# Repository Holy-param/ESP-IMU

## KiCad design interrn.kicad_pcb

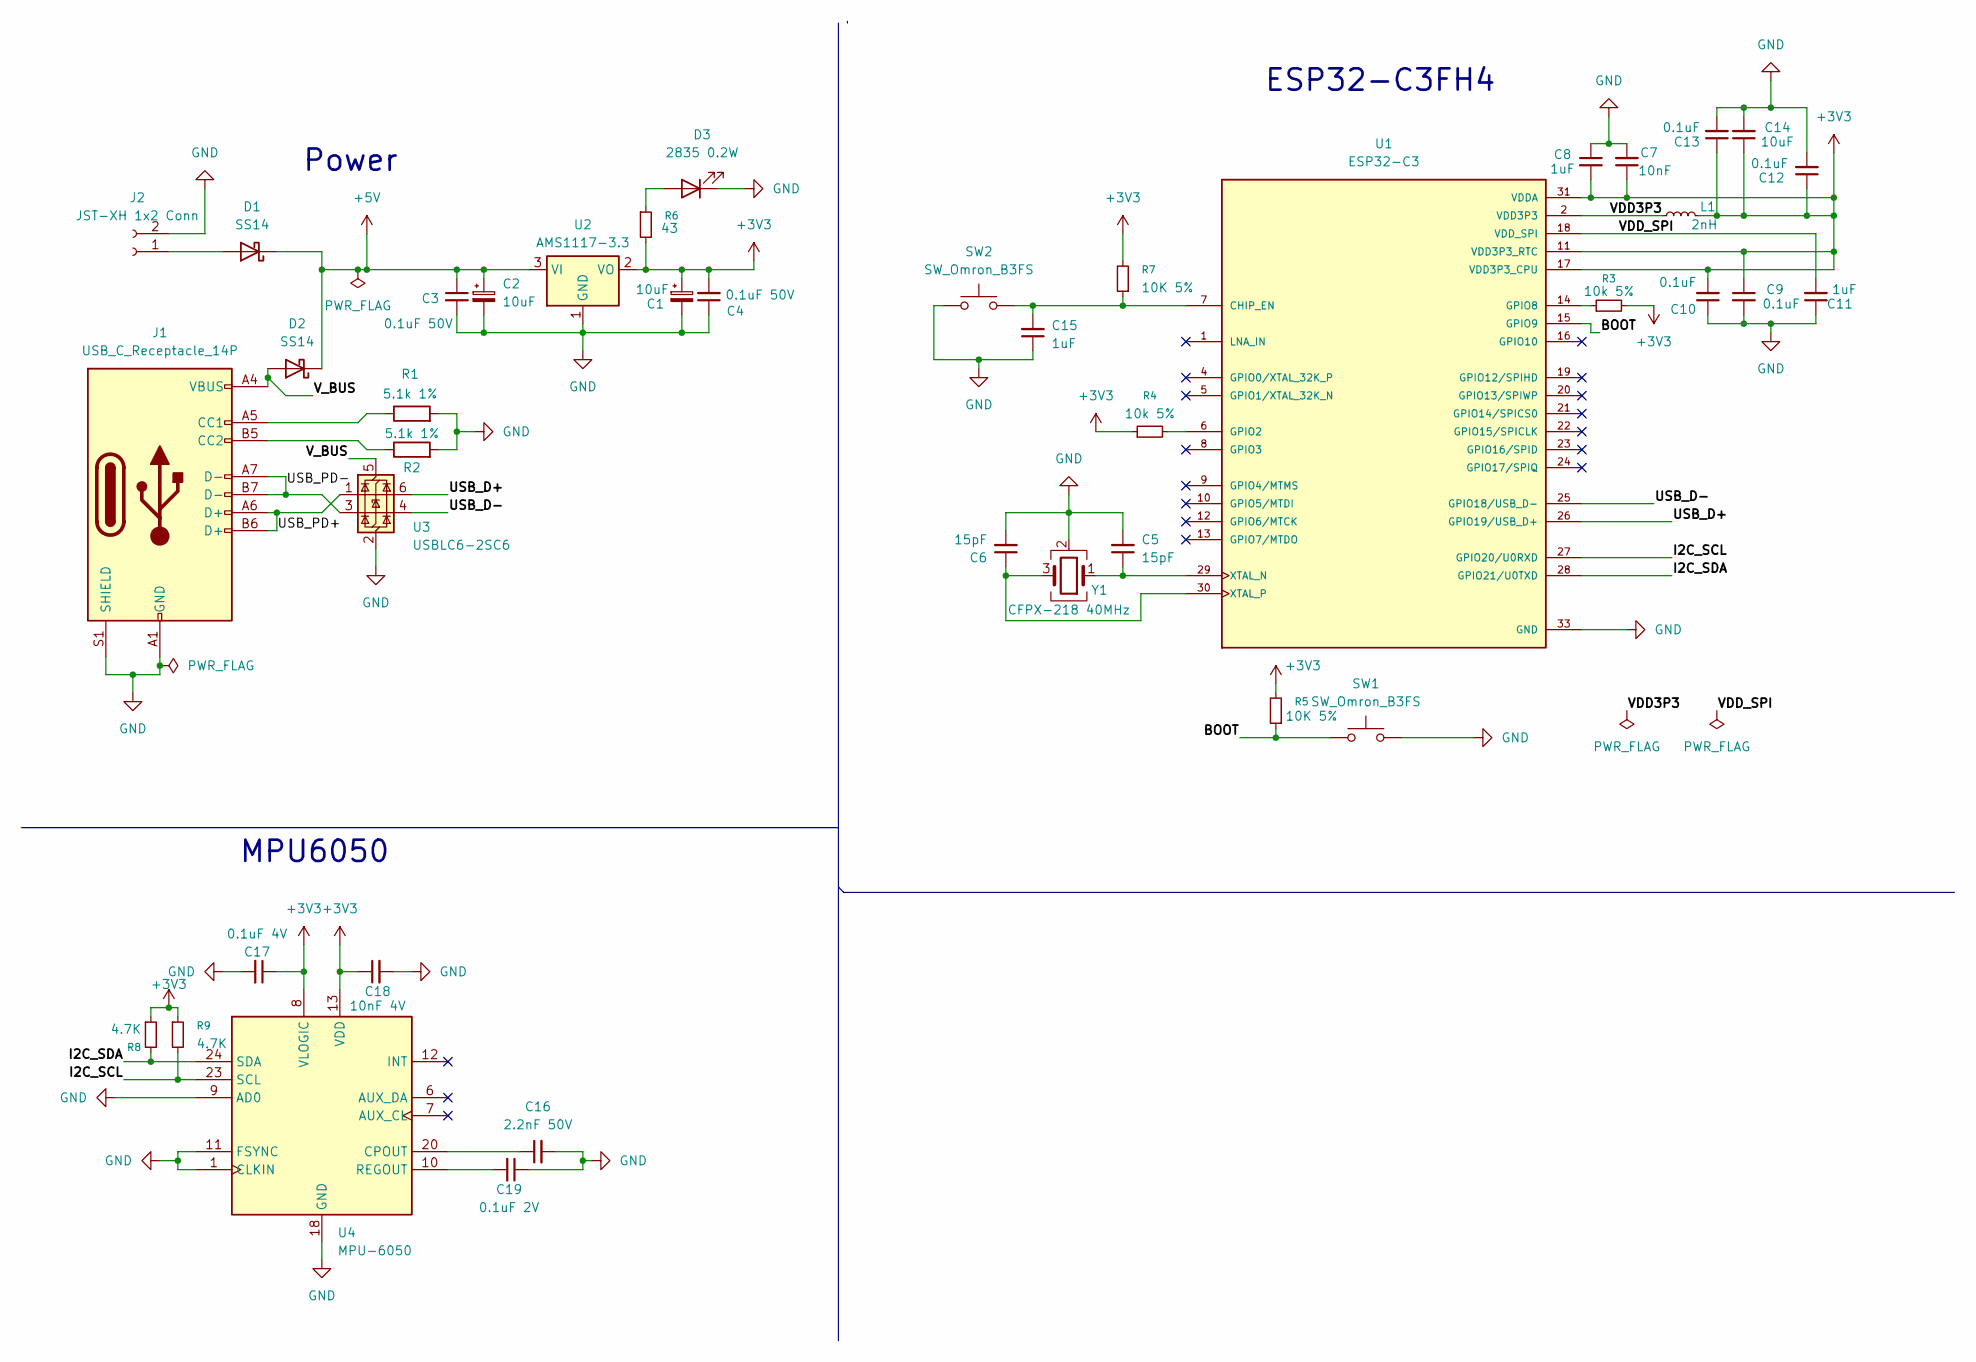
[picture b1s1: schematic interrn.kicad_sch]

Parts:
C1, C2: 10uF; CP_EIA-7343-15_Kemet-W
C3, C4: 0.1uF 50V; C_0402_1005Metric_Pad0.74x0.62mm_HandSolder
C5, C6: 15pF; C_0402_1005Metric
C7: 10nF; C_0402_1005Metric
C8, C11, C15: 1uF; C_0402_1005Metric
C9, C10, C12, C13: 0.1uF; C_0402_1005Metric
C14: 10uF; C_0402_1005Metric
C16: 2.2nF 50V; C_0402_1005Metric
C17: 0.1uF 4V; C_0402_1005Metric
C18: 10nF 4V; C_0402_1005Metric
C19: 0.1uF 2V; C_0402_1005Metric
D1, D2: SS14; D_SMA
D3: 2835 0.2W; LED_PLCC_2835
J1: USB_C_Receptacle_14P; USB_C_Receptacle_G-Switch_GT-USB-7010ASV
J2: JST-XH 1x2 Conn; JST_XH_B2B-XH-AM_1x02_P2.50mm_Vertical
L1: 2nH; L_0402_1005Metric
R1, R2: 5.1k 1%; R_0402_1005Metric
R3, R4: 10k 5%; R_0402_1005Metric
R5, R7: 10K 5%; R_0402_1005Metric
R6: 43; R_0402_1005Metric
R8, R9: 4.7K; R_0402_1005Metric
SW1, SW2: SW_Omron_B3FS; SW_SPST_Omron_B3FS-100xP
U1: ESP32-C3; QFN50P500X500X90-33N; MPN ESP32-C3
U2: AMS1117-3.3; SOT-223-3_TabPin2
U3: USBLC6-2SC6; SOT-23-6
U4: MPU-6050; InvenSense_QFN-24_4x4mm_P0.5mm
Y1: CFPX-218 40MHz; Crystal_SMD_WE_CFPX-218-4Pin_2.5x2.0mm

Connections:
+3V3: C1.1, C4.2, C7.1, C8.2, C9.1, C10.2, C12.1, C13.1, C14.1, C17.1, C18.1, L1.2, R3.2, R4.1, R5.2, R6.2, R7.2, R8.1, R9.1, U1.11 (VDD3P3_RTC), U1.17 (VDD3P3_CPU), U1.31 (VDDA), U1.32 (VDDA), U2.2 (VO), U4.8 (VLOGIC), U4.13 (VDD)
+5V: C2.1, C3.1, D1.1 (K), D2.1 (K), U2.3 (VI)
/BOOT: R5.1, SW1.1, U1.15 (GPIO9)
/I2C_SCL: R9.2, U1.27 (GPIO20/U0RXD), U4.23 (SCL)
/I2C_SDA: R8.2, U1.28 (GPIO21/U0TXD), U4.24 (SDA)
/USB_D+: U1.26 (GPIO19/USB_D+), U3.6 (I/O1)
/USB_D-: U1.25 (GPIO18/USB_D-), U3.4 (I/O2)
/USB_PD+: J1.A6 (D+), J1.B6 (D+), U3.1 (I/O1)
/USB_PD-: J1.A7 (D-), J1.B7 (D-), U3.3 (I/O2)
/VDD_SPI: C11.2, U1.18 (VDD_SPI)
/V_BUS: D2.2 (A), J1.A4 (VBUS), J1.A9 (VBUS), J1.B4 (VBUS), J1.B9 (VBUS), U3.5 (VBUS)
GND: C1.2, C2.2, C3.2, C4.1, C5.2, C6.2, C7.2, C8.1, C9.2, C10.1, C11.1, C12.2, C13.2, C14.2, C15.1, C16.2, C17.2, C18.2, C19.1, D3.1 (K), J1.A1 (GND), J1.A12 (GND), J1.B1 (GND), J1.B12 (GND), J1.S1 (SHIELD), J2.2, R1.2, R2.2, SW1.2, SW2.1, U1.33 (GND), U2.1 (GND), U3.2 (GND), U4.1 (CLKIN), U4.9 (AD0), U4.11 (FSYNC), U4.18 (GND), Y1.2 (G), Y1.4 (G)
unnamed: D1.2 (A), J2.1
unnamed: D3.2 (A), R6.1
unnamed: J1.A5 (CC1), R1.1
unnamed: J1.B5 (CC2), R2.1
unnamed: C15.2, R7.1, SW2.2, U1.7 (CHIP_EN)
unnamed: R4.2, U1.6 (GPIO2)
unnamed: R3.1, U1.14 (GPIO8)
unnamed: C5.1, U1.29 (XTAL_N), Y1.1
unnamed: C6.1, U1.30 (XTAL_P), Y1.3
unnamed: C16.1, U4.20 (CPOUT)
unnamed: C19.2, U4.10 (REGOUT)
VDD3P3: L1.1, U1.2 (VDD3P3), U1.3 (VDD3P3)

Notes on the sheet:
MPU6050
Power
ESP32-C3FH4

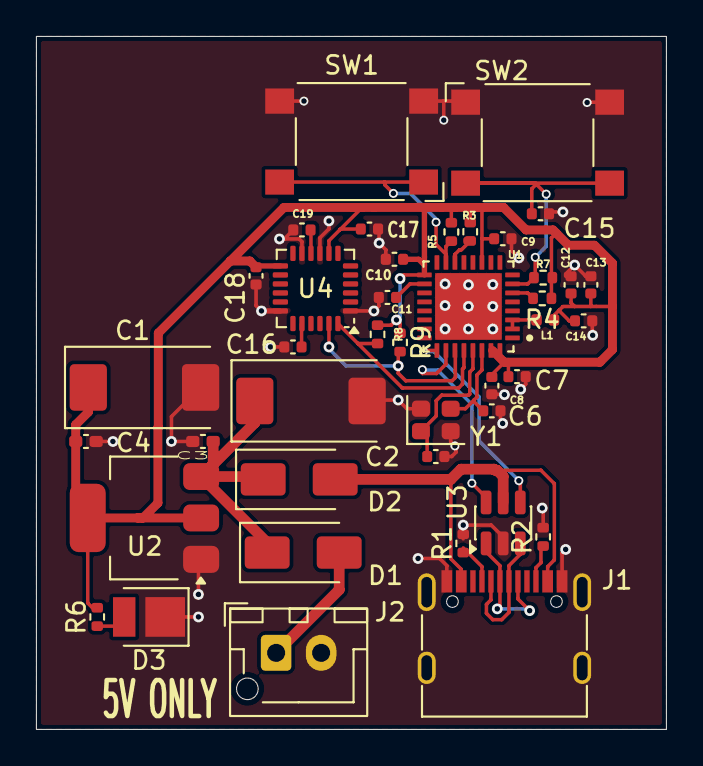
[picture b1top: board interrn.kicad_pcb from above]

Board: 2 copper layers, 35.0 x 38.5 mm, 41 parts (0 on the bottom side), 24 nets.
